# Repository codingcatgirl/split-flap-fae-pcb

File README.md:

# Split-Flap Fae PCB

This repository contains an alternative, improved, (near) drop-in replacement PCB for [David Kingsman's Split-Flap Display](https://github.com/Dave19171/split-flap). 

**Please note** that due to some changes in pinout, you need to use [evilscientress' improved fork of the firmware](https://github.com/evilscientress/split-flap), which was specifically created along with this PCB.

It provides the following Features:

- Identical PCB outline, connectors and connector positions.
- Removed Arduino Nano, use its Atmega328P directly, saving cost and space.
- Run the Atmega328P on 3V3, removing the need for a 5V rail and logic conversion and increasing power efficiency by using a step-down converter (TPS5430). The entire assembly runs on 3V3 logic now.
- Removed the ESP-12F module and use its ESP8266 chip directly, simplifying the PCB again.
- Added ISP and Serial headers to flash both chips.
- Added more jumpers for address configuration, so displays with more than 16 modules could be built in theory, if the firmware supports it.
- Added an additional connector that could be used to connect WS2815 (12V) LED strip.
- Full compatibility with JLCPCB's SMT assembly service.

## How to order the PCBs:
- Use the gerber files in the `fab` folder for the PCB.
- Use the BOM and top-pos files in the `fab` folder for assembly.
- **Deselect assembly for the ESP2866 module, since you need it on one PCB only. You should solder it on yourself.**
  - To omit the ESP2866 module, deselect U4.
  - To omit the serial pin header for the ESP2866 module, deselect J8.
  - Other parts that are also only needed for the ESP2866 are R5, R6, R7, R8, C5, and C6. However, since these are very tedious to manually solder and having JLCPCB assemble them costs close to nothing, i recommend keeping them in.

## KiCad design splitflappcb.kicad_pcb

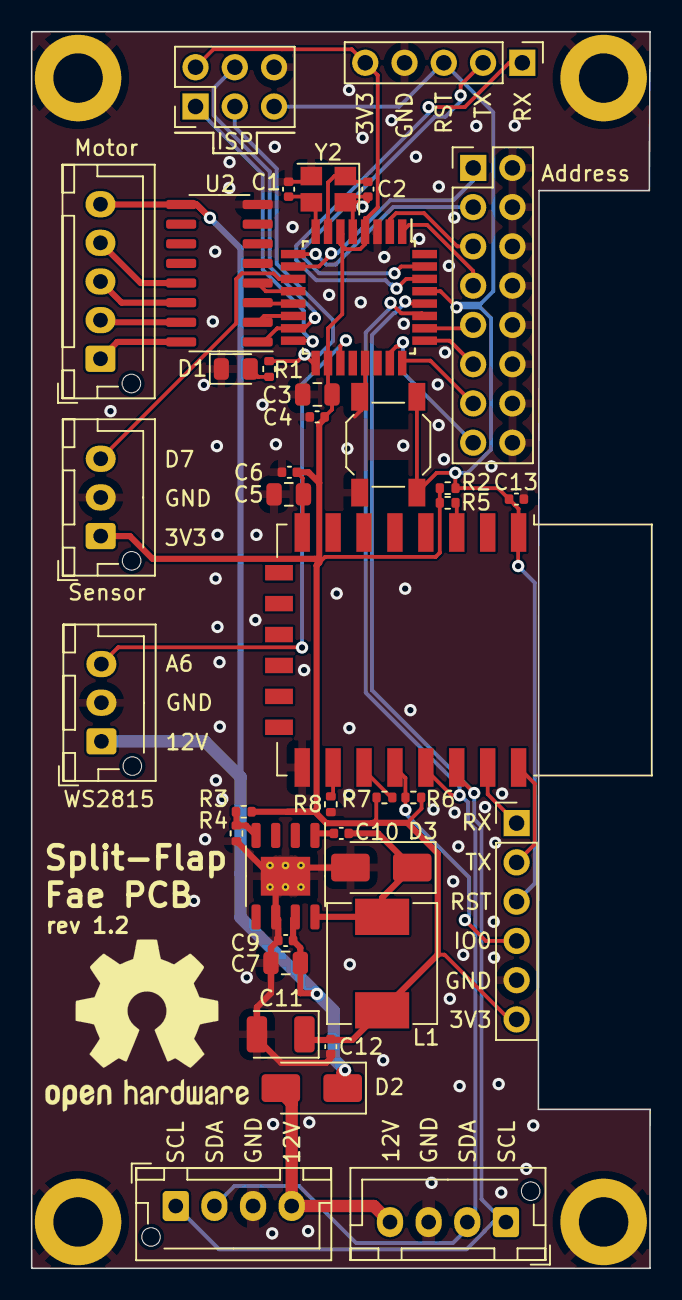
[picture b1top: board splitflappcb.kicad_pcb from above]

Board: 2 copper layers, 40.0 x 80.0 mm, 43 parts (0 on the bottom side), 41 nets.

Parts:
C1, C2: 22pF; C_0402_1005Metric
C3, C5, C7: 10uF; C_0805_2012Metric
C4, C6, C9, C10, C12, C13: 100n; C_0402_1005Metric
C11: 220uF; CP_EIA-3528-21_Kemet-B
D1: LED; LED_0805_2012Metric
D2, D3: SS54; D_SMA
H1, H2, H3, H4: MountingHole_Pad; MountingHole_3.2mm_M3_DIN965_Pad
J1, J2: Conn_01x04_Pin; JST_XH_B4B-XH-AM_1x04_P2.50mm_Vertical
J3: Conn_01x05_Pin; JST_XH_B5B-XH-AM_1x05_P2.50mm_Vertical
J4: AddressJumpers; PinHeader_2x08_P2.54mm_Vertical
J5: HallSensor; JST_XH_B3B-XH-AM_1x03_P2.50mm_Vertical
J6: AVR-ISP-6; PinHeader_2x03_P2.54mm_Vertical
J7: Serial-328P; PinHeader_1x05_P2.54mm_Vertical
J8: Serial-ESP12E; PinHeader_1x06_P2.54mm_Vertical
J9: WS2815; JST_XH_B3B-XH-AM_1x03_P2.50mm_Vertical
L1: 47uH; L_Chilisin_BMRx00060630
R1: 220; R_0402_1005Metric
R2, R3, R5, R6, R7, R8: 10k; R_0402_1005Metric
R4: 5k9; R_0402_1005Metric
SW1: RESET; SW_SPST_SKQG_WithStem
U1: TPS5430; SOIC-8-1EP_3.9x4.9mm_P1.27mm_EP2.514x3.2mm_ThermalVias
U2: ULN2003A; SOIC-16_3.9x9.9mm_P1.27mm
U3: ATmega328P-A; TQFP-32_7x7mm_P0.8mm
U4: ESP-12E
Y2: 16MHz; Crystal_SMD_3225-4Pin_3.2x2.5mm

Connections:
+3V3: C3.2, C4.2, C5.2, C6.2, C11.1, C12.1, J5.1, J6.2 (VCC), J7.5, J8.6, L1.2, R2.1, R3.1, R5.1, R6.1, R7.1, U3.4 (VCC), U3.6 (VCC), U3.18 (AVCC), U4.8 (VCC)
+12V: C7.1, C9.1, D2.1 (K), J3.5, J9.1, U1.7 (VIN), U2.9 (COM)
/01-EN: R5.2, U4.3 (EN)
/01-IO0: J8.4, R6.2, U4.18 (GPIO0)
/01-IO2: R7.2, U4.17 (GPIO2)
/01-RX: J8.1, U4.21 (GPIO3/RXD)
/01-TX: J8.2, U4.22 (GPIO1/TXD)
/A0: J4.15, U3.23 (PC0)
/A1: J4.13, U3.24 (PC1)
/A2: J4.11, U3.25 (PC2)
/A3: J4.9, U3.26 (PC3)
/A4/SDA: J1.2, J2.2, U3.27 (PC4), U4.19 (GPIO4)
/A5/SCL: J1.1, J2.1, U3.28 (PC5), U4.20 (GPIO5)
/A6: J9.3, U3.19 (ADC6)
/D0: J7.1, U3.30 (PD0)
/D1: J7.2, U3.31 (PD1)
/D3: J4.7, U3.1 (PD3)
/D4: J4.5, U3.2 (PD4)
/D5: J4.3, U3.9 (PD5)
/D6: J4.1, U3.10 (PD6)
/D7: J5.3, U3.11 (PD7)
/D8: U2.4 (I4), U3.12 (PB0)
/D9: U2.3 (I3), U3.13 (PB1)
/D10: U2.2 (I2), U3.14 (PB2)
/D11: J6.4 (MOSI), U2.1 (I1), U3.15 (PB3)
/D12: J6.1 (MISO), U3.16 (PB4)
/D13: J6.3 (SCK), R1.2, U3.17 (PB5)
/RESET: C13.2, J6.5 (~RST), J7.3, J8.3, R2.2, SW1.1, U3.29 (~RESET/PC6), U4.1 (~RST)
GND: C1.1, C2.1, C3.1, C4.1, C5.1, C6.1, C7.2, C9.2, C11.2, C12.2, C13.1, D1.1 (K), D3.2 (A), H1.1, H2.1, H3.1, H4.1, J1.3, J2.3, J4.2, J4.4, J4.6, J4.8, J4.10, J4.12, J4.14, J4.16, J5.2, J6.6 (GND), J7.4, J8.5, J9.2, R4.2, R8.2, SW1.2, U1.6 (GND), U1.9 (PwPad), U2.8 (GND), U3.3 (GND), U3.5 (GND), U3.21 (GND), U4.15 (GND), Y2.2, Y2.4
unnamed: D1.2 (A), R1.1
unnamed: D2.2 (A), J1.4, J2.4
unnamed: C10.1, D3.1 (K), L1.1, U1.8 (PH)
unnamed: J3.1, U2.16 (O1)
unnamed: J3.2, U2.15 (O2)
unnamed: J3.3, U2.14 (O3)
unnamed: J3.4, U2.13 (O4)
unnamed: C10.2, U1.1 (BOOT)
unnamed: R3.2, R4.1, U1.4 (VSNS)
unnamed: C2.2, U3.7 (XTAL1/PB6), Y2.1
unnamed: C1.2, U3.8 (XTAL2/PB7), Y2.3
unnamed: R8.1, U4.16 (GPIO15)

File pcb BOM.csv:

"Source:","/home/laura/Projekte/bettersplitflap/pcb/pcb.kicad_sch"
"Date:","Fri 10 Nov 2023 12:23:47 AM CET"
"Tool:","Eeschema 7.0.8"
"Generator:","/usr/share/kicad/plugins/bom_csv_grouped_by_value.py"
"Component Count:","35"

"Collated Components:"

"Item","Qty","Reference(s)","Value","LibPart","Footprint","Datasheet","DNP","DIGIKEY","LCSC","MPR"
"1","2","C1, C2","22pF","Device:C_Small","Capacitor_SMD:C_0402_1005Metric","~","","","C1555",""
"2","3","C3, C5, C7","10uF","Device:C_Small","Capacitor_SMD:C_0805_2012Metric","~","","","C440198",""
"3","5","C4, C6, C9, C10, C12","100n","Device:C_Small","Capacitor_SMD:C_0402_1005Metric","~","","","C307331",""
"4","1","C11","220uF","Device:C_Polarized_Small","Capacitor_Tantalum_SMD:CP_EIA-3528-21_Kemet-B","~","","P16245CT-ND","C79111","6TPE220MAZB"
"5","1","D1","LED","Device:LED","LED_SMD:LED_0805_2012Metric","~","","","C2297",""
"6","2","D2, D3","SS54","Device:D_Schottky","Diode_SMD:D_SMA","~","","","C22452",""
"7","2","J1, J2","Conn_01x04_Pin","Connector:Conn_01x04_Pin","Connector_JST:JST_XH_B4B-XH-AM_1x04_P2.50mm_Vertical","~","","","C161871",""
"8","1","J3","Conn_01x05_Pin","Connector:Conn_01x05_Pin","Connector_JST:JST_XH_B5B-XH-AM_1x05_P2.50mm_Vertical","~","","","C161872",""
"9","1","J4","AddressJumpers","Connector_Generic:Conn_02x08_Odd_Even","Connector_PinHeader_2.54mm:PinHeader_2x08_P2.54mm_Vertical","~","","","C2685187",""
"10","1","J5","HallSensor","Connector:Conn_01x03_Pin","Connector_JST:JST_XH_B3B-XH-AM_1x03_P2.50mm_Vertical","~","","","C144394",""
"11","1","J6","AVR-ISP-6","Connector:AVR-ISP-6","Connector_PinHeader_2.54mm:PinHeader_2x03_P2.54mm_Vertical"," ~","","","C65114",""
"12","1","J7","Serial-328P","Connector:Conn_01x05_Pin","Connector_PinHeader_2.54mm:PinHeader_1x05_P2.54mm_Vertical","~","","","C492404",""
"13","1","J8","Serial-ESP12E","Connector:Conn_01x05_Pin","Connector_PinHeader_2.54mm:PinHeader_1x05_P2.54mm_Vertical","~","","","C492404",""
"14","1","J9","WS2812","Connector:Conn_01x03_Pin","Connector_JST:JST_XH_B3B-XH-AM_1x03_P2.50mm_Vertical","~","","","C144394",""
"15","1","L1","47uH","Device:L","Inductor_SMD:L_Chilisin_BMRx00060630","~","","","C475913",""
"16","1","R1","220","Device:R_Small","Resistor_SMD:R_0402_1005Metric","~","","","C25091",""
"17","2","R2, R5","1K","Device:R_Small","Resistor_SMD:R_0402_1005Metric","~","","","C11702",""
"18","1","R3","10k","Device:R_Small","Resistor_SMD:R_0402_1005Metric","~","","","C25744",""
"19","1","R4","5k9","Device:R_Small","Resistor_SMD:R_0402_1005Metric","~","","","C273691",""
"20","1","SW1","SW_Push","Switch:SW_Push","Button_Switch_SMD:SW_SPST_SKQG_WithStem","~","","","C318884",""
"21","1","U1","TPS5430","opendcc:TPS5450","Package_SO:SOIC-8-1EP_3.9x4.9mm_P1.27mm_EP2.514x3.2mm_ThermalVias","https://www.ti.com/lit/ds/symlink/tps5450.pdf","","","C9864",""
"22","1","U2","ULN2003A","Transistor_Array:ULN2003A","Package_SO:SOIC-16_3.9x9.9mm_P1.27mm","http://www.ti.com/lit/ds/symlink/uln2003a.pdf","","","C7512",""
"23","1","U3","ATmega328P-A","MCU_Microchip_ATmega:ATmega328P-A","Package_QFP:TQFP-32_7x7mm_P0.8mm","http://ww1.microchip.com/downloads/en/DeviceDoc/ATmega328_P%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","","","C14877",""
"24","1","U4","ESP-12E","RF_Module:ESP-12E","RF_Module:ESP-12E","http://wiki.ai-thinker.com/_media/esp8266/esp8266_series_mod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","","","C89297",""
"25","1","Y2","16MHz","Device:Crystal_GND24_Small","Crystal:Crystal_SMD_3225-4Pin_3.2x2.5mm","~","","","C13738",""

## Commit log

2023-11-10 rev1.0
2024-04-14 add schematic and pcb rendering, remove empty csv
2024-04-14 added image to readme
2024-04-14 Create LICENSE
2024-05-15 rev 1.2 – fix incorrect pin labels on ISP connector (fixes #1)
2024-06-24 add note about firmware fork
